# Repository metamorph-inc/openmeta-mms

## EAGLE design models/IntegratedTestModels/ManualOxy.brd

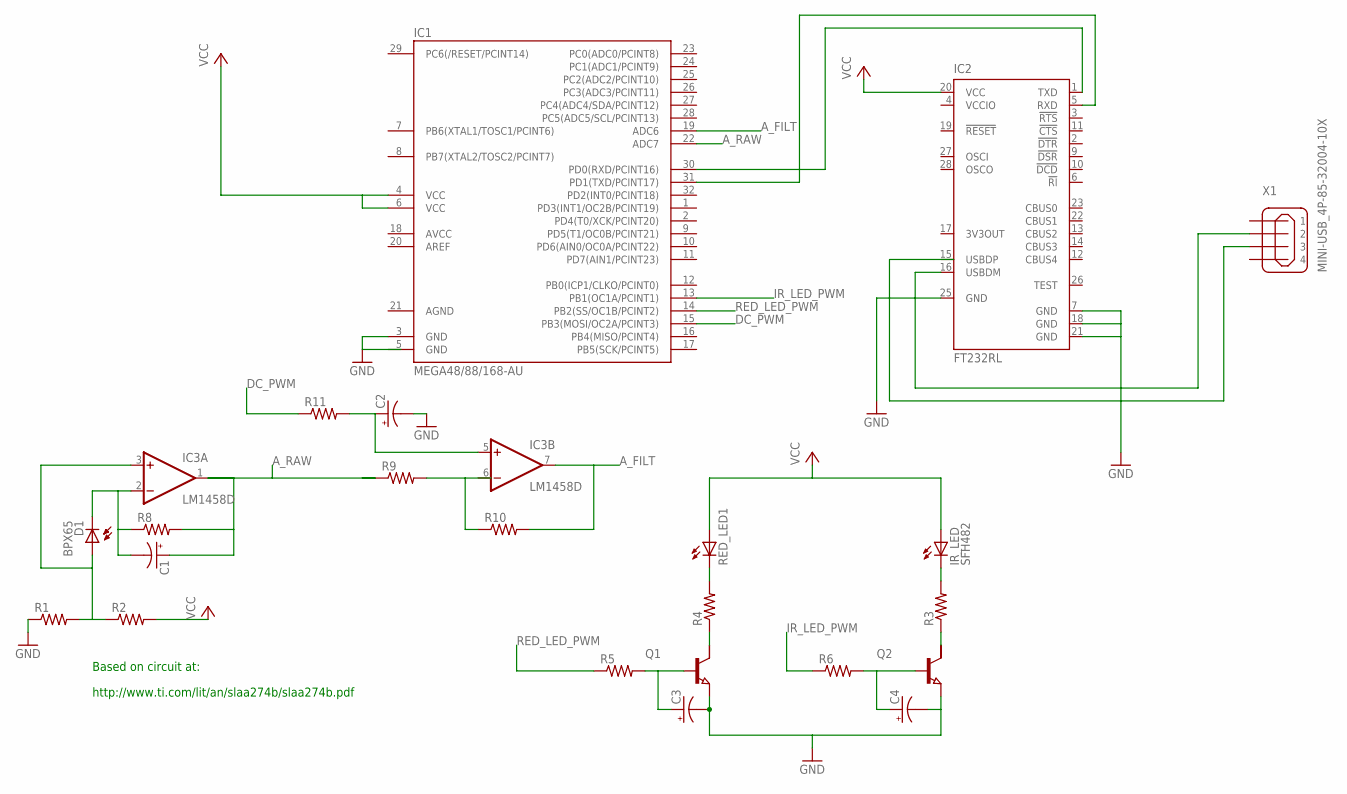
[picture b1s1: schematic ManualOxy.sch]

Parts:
C1, C2, C3, C4: CPOL-US153CLV-0810; 153CLV-0810
D1: BPX65
IC1: MEGA48/88/168-AU; TQFP32-08
IC2: FT232RL; SSOP28
IC3: LM1458D; SO08
IR_LED: SFH482
Q1, Q2: NPN-TRANSISTIOR-2COLSOT143; SOT143
R1, R2, R3, R4, R5, R6, R8, R9, R10, R11: R-US_M2012; M2012
RED_LED1: LED10MM
X1: MINI-USB_4P-85-32004-10X; 85-32004-10X

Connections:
AGND: IC1.21 (AGND)
A_FILT: IC3.7 (OUT), R10.2
A_RAW: C1.+, IC3.1 (OUT), R8.2, R9.1
DC_PWM: IC1.15 (PB3(MOSI/OC2A/PCINT3))
GND: C2.-, C3.-, C4.-, IC1.3 (GND), IC1.5 (GND), IC2.7 (GND), IC2.18 (GND), IC2.21 (GND), IC2.25 (GND), Q1.3 (E), Q2.3 (E), R1.1
IR_LED_PWM: IC1.13 (PB1(OC1A/PCINT1))
unnamed: IC1.30 (PD0(RXD/PCINT16)), IC2.1 (TXD)
unnamed: IC1.31 (PD1(TXD/PCINT17)), IC2.5 (RXD)
unnamed: IC2.16 (USBDM), X1.2
unnamed: Q1.2 (C), R4.1
unnamed: R4.2, RED_LED1.K (C)
unnamed: IR_LED.K (C), R3.2
unnamed: Q2.2 (C), R3.1
unnamed: D1.A, IC3.3 (+IN), R1.2, R2.1
unnamed: C1.-, D1.K (C), IC3.2 (-IN), R8.1
unnamed: R9.2, R10.1
unnamed: C2.+, IC3.5 (+IN), R11.2
unnamed: C3.+, Q1.1 (B), R5.2
unnamed: C4.+, Q2.1 (B), R6.2
RED_LED_PWM: IC1.14 (PB2(SS/OC1B/PCINT2))
V+: IC3.8 (V+)
V-: IC3.4 (V-)
VCC: IC1.4 (VCC), IC1.6 (VCC), IC2.20 (VCC), IR_LED.A, R2.2, RED_LED1.A
VCCIO: IC2.4 (VCCIO)

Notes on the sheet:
http://www.ti.com/lit/an/slaa274b/slaa274b.pdf
Based on circuit at:

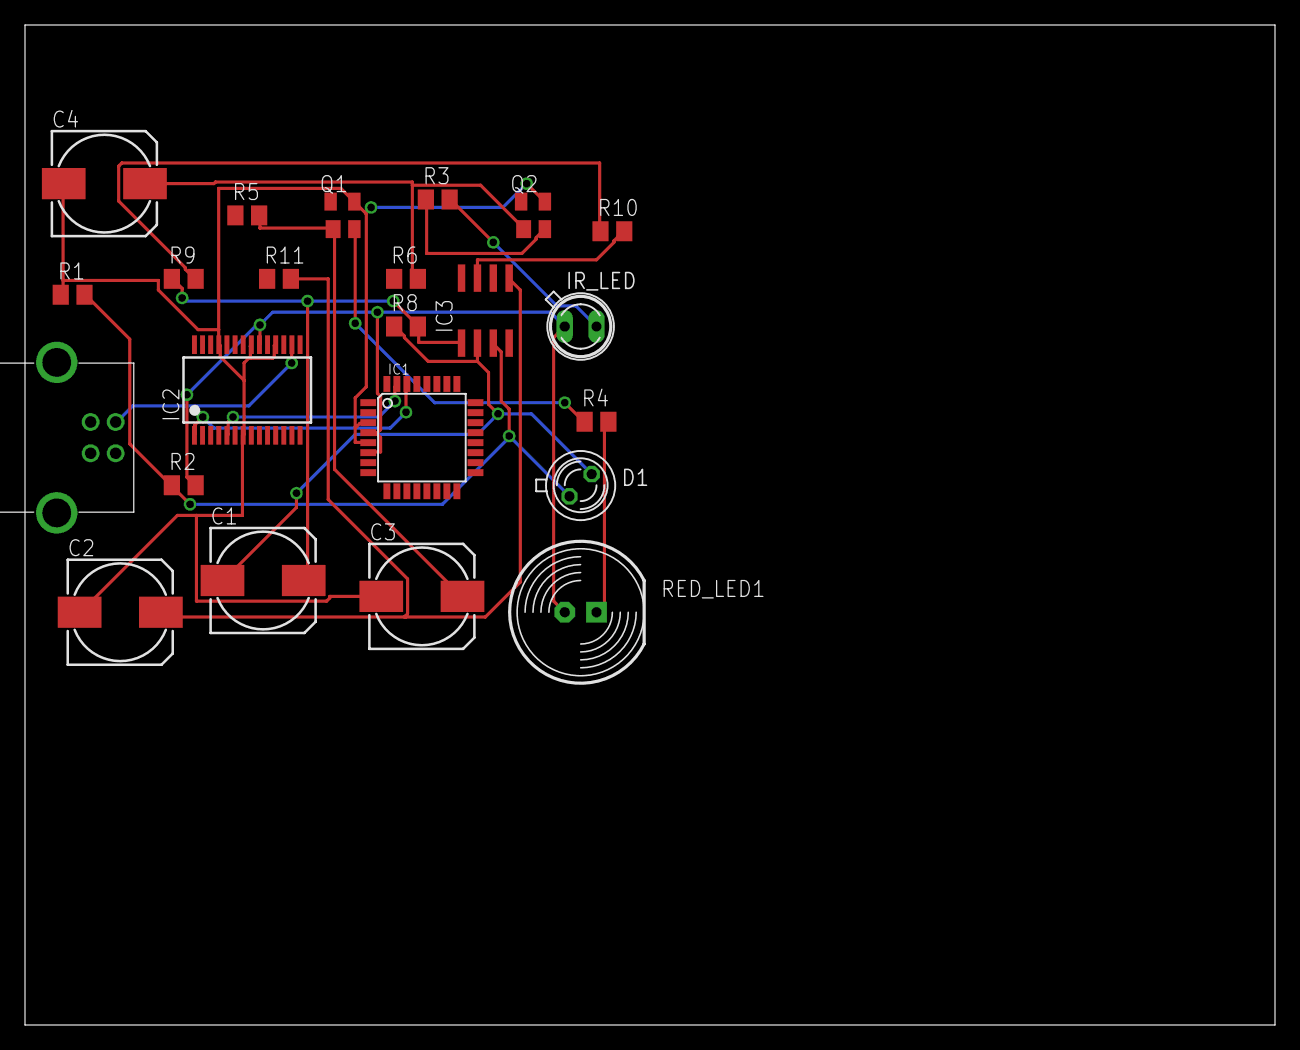
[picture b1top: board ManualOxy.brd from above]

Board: 2 copper layers, 100.0 x 80.0 mm, 23 parts (0 on the bottom side), 17 nets.

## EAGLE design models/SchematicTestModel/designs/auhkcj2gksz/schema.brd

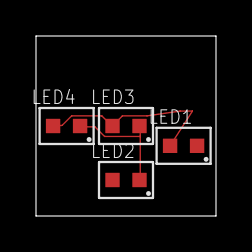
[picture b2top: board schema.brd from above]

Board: 2 copper layers, 10.0 x 10.0 mm, 4 parts (0 on the bottom side), 2 nets.

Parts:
LED1, LED2, LED3, LED4: LTST-C191KRKT; LED

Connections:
unnamed: LED1.ANODE, LED3.ANODE, LED4.ANODE
unnamed: LED2.CATHODE, LED3.CATHODE, LED4.CATHODE
